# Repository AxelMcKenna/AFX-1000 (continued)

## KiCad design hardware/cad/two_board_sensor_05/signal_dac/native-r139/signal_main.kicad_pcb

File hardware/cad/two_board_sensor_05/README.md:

# TBH05 sensor carrier and magnet escape barrier

**Current spring completion candidate:** see [SPRING.md](SPRING.md) for the selected spring, positive custom clevis-pin anchors, replacement bracket/arm and final `spring-verified-r2` evidence. The r3 carrier below remains unchanged. Its original-anchor spring discussion is retained as reference and superseded by that add-on.

This is a new **unpowered mechanical interface candidate**, fitted to the unchanged TBH01 r6 housing and TBH03 r5 lever. It closes the modeled carrier attachment and adds positive axial magnet capture. It does **not** supply a routed/populated angle-sensor PCB, a qualified magnet bond, or a selected return spring.

The existing source specified a custom AS5600 PCB reserve, not an off-the-shelf board. This design therefore specifies a **new 20 × 18 × 1.6 mm PCB**, instead of guessing holes in an existing board. Its sensor axis is unchanged at Y82/Z31.6. The original 20 mm-tall reserve had insufficient room for an actual top clamp below the button guide; shortening its top edge by 2 mm fixes that interface. A PCB designer must accept and implement this contract before printing for an actual populated board.

## Files and geometry

- `carrier.scad`: editable geometry. `tbh05_installed()` exposes the complete nominal assembly, hardware-head and electrical-envelope allocations for integration. Include the source with a nonmatching `part` selector, or use modules with all inherited housing definitions available.
- `mechanical-contract.json`: dimensions, PCB edge keepouts, component/lead/wiring reserves, fasteners and spring geometry.
- `verified-r3/review.json`: final native cases and recursively bound source hashes. Nine empty interference checks, two printable solids and one positive magnet-capture control.
- `verified-r3/sensor_carrier/sensor_carrier.stl` and `verified-r3/sensor_cap/sensor_cap.stl`: native print candidates, millimetres, base at Z0.
- `preview-r3.png`: exact exported carrier/cap meshes with the nominal custom PCB/package and original lever; omitted wiring/spring/fasteners are identified.
- `analysis.py`, `run.py`, `preview.py`: regenerate scalar evidence, isolated native checks and preview. Run native checks with a fresh output name; prior evidence is never overwritten.

The carrier uses the existing **left lever bolts at (306,69) and (306,102)**. Replace those two M3×20 bolts with **M3×25** and retain 0.5 mm washers, head OD≤5.5 mm and washer OD≤7 mm. The 2 mm feet sit on top of the existing bracket. Screw tips reach Z−4.9, giving 1.1 mm nominal clearance with the existing ≥6 mm feet. Measure actual thread engagement and tip clearance.

Two horizontal **M2×5 screws**, head OD≤3.8 mm and height≤2 mm, secure the removable cap. Tap the two Ø1.6 pilots M2 after printing. The cap enters from above; its tabs lie outside the end rails, so no screw passes through the PCB. Do not substitute taller vertical cap screws: the guide is directly above this assembly. Inspect the thin features, holes and magnet-barrier supports in the slicer; no printer/material process is qualified here.

## Sensor PCB receiving contract

The board is vertical: X299.7..301.3, Y72..92, Z21.6..39.6. It slides into 2 mm-wide X slots with no drilled mounting holes. Nominal 1.6 mm stock and the 1.5–1.7 mm receiving interval leave play; printed dimensions must be measured and shims or a dimensionally corrected carrier used to achieve alignment. Do not infer precise sensor centering from loose slots.

Keep both Y-edge margins and top/bottom margins free of copper, pads and components as specified in the JSON. The sensor and its lands receive a conservative 6.4 × 6.4 mm YZ envelope, projecting 1.75 mm toward +X. That is an allocation, not an approved supplier maximum. The board rear has a 1.5 mm-deep central population/lead reserve and a separate X293.7..299.7/Y76..88/Z23..28 wiring/connector reserve. The eventual board and selected connector must fit those bounds or the carrier must be revised. The rest of the harness is not defined by this local reserve.

Insert the populated board with the cap removed. Its component side faces the magnet (+X). There is no retained board polarity/connector design yet. After assembly, confirm the package center actually aligns to Y82/Z31.6 and measure the magnet/package gap throughout lever endplay.

## Magnet capture and magnetic alignment

A stationary polymer ring lies at X303.5..304.3, with a Ø4 opening in front of the existing Ø6 magnet pocket. It blocks a Ø6 magnet from leaving axially. The ring and both supports are physically part of the carrier, not floating preview geometry. The native positive control overlaps the barrier with an escaping magnet; full lever sweep includes ±0.5 mm axial motion and the earlier 0.1 mm rotor expansion.

**The ring does not transmit torque.** A compatible selected adhesive and verified bond to the rotor are still required; a loose magnet can remain captured while giving a wrong angle. Install and bond the magnet before fitting the carrier. Do not change magnet thickness or polarity silently: the existing pocket is for Ø6 × 2 mm diametric magnetization. Grade, dimensional tolerances, adhesive compatibility, retention under shock and the magnetic field remain unqualified.

At the allocated package face and a nominal seated magnet front of X305.1, the nominal physical gap is 2.05 mm, ranging 1.55–2.55 mm across the ±0.5 mm geometric allowance. This arithmetic does not prove acceptable field strength. The manufacturer's [AS5600 evaluation-board manual](https://look.ams-osram.com/m/4f8342513a447495/original/AS5600_UG000254_2-00.pdf) illustrates a nonmagnetic holder, a 6 × 2.5 mm reference magnet and 0.5–2.5 mm gap; it instructs alignment using the AGC reading. Its reference magnet is **not** the current 2 mm-thick design magnet. Select and test the actual magnet, verify magnet-present/field status and angle through the full stroke, and adjust the carrier if required.

## Return spring: concrete remaining work

The unchanged fixed eye is (316,70,35.6); the rotating eye follows (316,82+10sin(a),31.6+10cos(a)). Eye spacing rises monotonically from **13.4164 to 18.2243 mm** over 0–35°, requiring **4.8079 mm travel**. The restoring moment arm is 8.9443 to 6.6527 mm. `analysis.py` checks the geometry independently; a conservative Ø4.02 mm corridor covers a ≤4 mm spring through continuous motion using hulls between 1° poses (0.01 mm radial reserve exceeds the chord error).

That corridor clears the modeled shell, controls, PCB envelopes and new carrier. It is not the actual spring, hooks or attachment design. The existing Ø2.2 cross holes do not automatically accept a catalogue spring's closed loops. Final spring selection needs the actual hook/clevis attachment geometry, preload, load/stroke rating, fatigue life and desired hand force; then repeat the local anchor/lever interference and physical return tests. The [Lee Spring catalogue](https://www.leespring.fr/download/Lee_Spring_Catalog_US_Eng.pdf) provides dimensional/load candidates, but no catalogue part has been adopted or ordered here.

## Validation scope and remaining gates

Final native evidence checks nominal carrier/cap/PCB allocations and hardware heads against shell, current component/lead envelopes, controls and the expanded moving lever. The intentional bracket seating contact uses the same 0.01 mm contact-plane exclusion as earlier packages. These are geometric checks, not a blanket manufacturing tolerance proof.

Remaining gates are: accept and electrically implement the custom sensor PCB and connector; select magnet/adhesive and exact spring/hooks; verify actual print fit, alignment, AGC/field status, rotation, return force, wear and retention; integrate the full harness. No powered or full-unit fabrication release is claimed. Prior r6/r5 packages were not modified.

Trial01 failed at sandbox Docker socket access and trial02 found the daemon stopped; no CAD process started in either case. These are recorded separately from CAD failures. Trial03 found an actual cap/guide interference; trial04 corrected it, and subsequent revisions strengthened cap screw bosses and added explicit electrical envelopes. Only `verified-r3` is the current evidence.

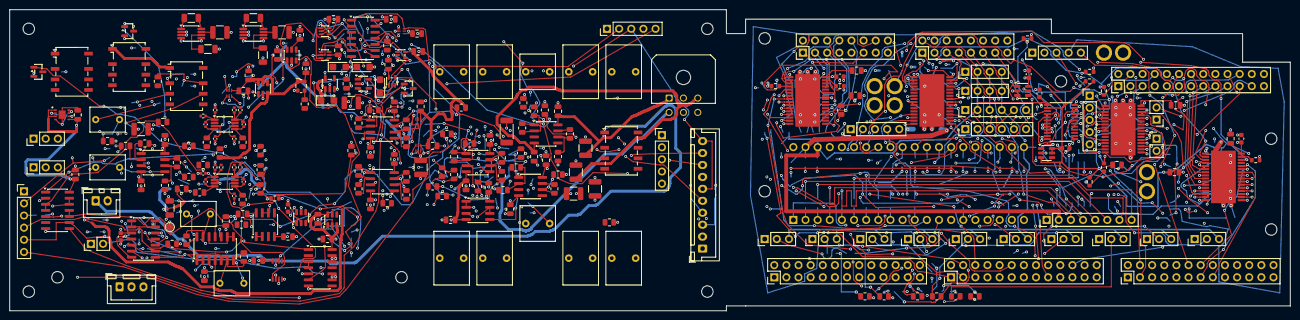
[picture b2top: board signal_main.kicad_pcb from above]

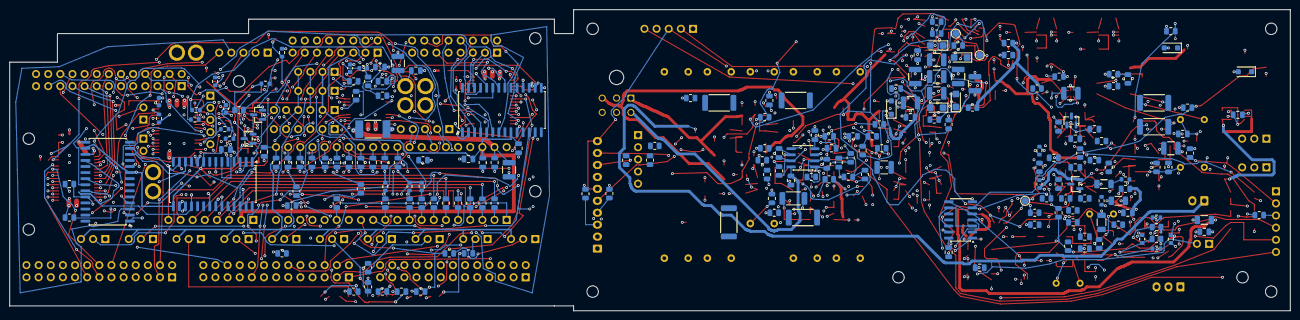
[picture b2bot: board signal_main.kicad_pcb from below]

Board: 8 copper layers, 268.0 x 63.0 mm, 477 parts (202 on the bottom side), 369 nets.

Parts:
A_C101, A_C102, A_C115, A_C116: 1pF C0G +/-0.1pF; C_0402_1005Metric
A_C103, A_C117: 47pF C0G 5%; C_0805_2012Metric
A_C104, A_C105, A_C118, A_C119: 22pF C0G 5%; C_0805_2012Metric
A_C106, A_C120: 100nF 25V X7R; C_0805_2012Metric
A_C107, A_C121: 1uF 63V film 10%; C_Rect_L7.2mm_W5.0mm_P5.00mm
A_C108, A_C122: 10uF 16V X7R; C_1206_3216Metric
A_C109, A_C123: 47uF 25V X7S; C_1210_3225Metric
A_C110, A_C111, A_C124, A_C125: 47uF 6.3V X7S; C_1206_3216Metric
A_C112, A_C126: 2.2uF 16V X7R; C_0805_2012Metric
A_C113, A_C114, A_C127, A_C128: 100nF 16V X7R; C_0402_1005Metric
A_C129, A_C130, A_C131, A_C132, A_C220, A_C221, A_C222, A_C223, A_C224, A_C225, A_C226, A_C228, A_C229, A_C311, A_C312, A_C313, A_C314, A_C315, A_C316, A_C317, A_C318, A_C323, A_C324, A_C405, A_C406, A_C505, A_C506, A_C507, A_C508: 100nF 50V X7R; C_0805_2012Metric
A_C133, A_C134: 10uF 50V X7R; C_1206_3216Metric
A_C135, A_C136: 100nF 16V X7R; C_0603_1608Metric
A_C201, A_C202, A_C205: 1uF 10V X7R 10%; C_0805_2012Metric
A_C203, A_C210, A_C212, A_C214: 100nF 50V C0G 5%; C_1210_3225Metric
A_C204, A_C206, A_C207, A_C208, A_C209, A_C211, A_C213, A_C215: 1uF 10V tantalum 10%; CP_EIA-3216-18_Kemet-A
A_C216, A_C218, A_C227: 2.2uF 25V X7R 10%; C_1210_3225Metric
A_C217, A_C219: 10uF 16V X7R 10%; C_1210_3225Metric
A_C230, A_C231, A_C232, A_C610, A_C611, A_C612: 100nF 16V X7R; C_0805_2012Metric
A_C301, A_C302, A_C306, A_C307: 510pF 50V C0G 2%; C_0805_2012Metric
A_C303, A_C308: 51pF 50V C0G 2%; C_0805_2012Metric
A_C304, A_C305, A_C309, A_C310: 1nF 50V C0G 1%; C_0805_2012Metric
A_C319, A_C320, A_C509, A_C510, A_C511, A_C512: 10uF 50V X7R; C_1210_3225Metric
A_C321, A_C322: 2.2uF film 63V 10%; C_Rect_L7.2mm_W7.2mm_P5.00mm_FKS2_FKP2_MKS2_MKP2
A_C401, A_C403: 1uF film 63V 10%; C_Rect_L7.2mm_W5.0mm_P5.00mm
A_C402, A_C404: 47pF 50V C0G 5%; C_0805_2012Metric
A_C407, A_C408: 10uF 50V X7R 10%; C_1210_3225Metric
A_C501, A_C502, A_C503, A_C504, A_C513, A_C514, A_C515, A_C516: 4.7uF film 63V 10%; C_Rect_L7.2mm_W11.0mm_P5.00mm_FKS2_FKP2_MKS2_MKP2
A_C601: 150pF C0G 5%; C_0805_2012Metric
A_C602, A_C603, A_C604, A_C605, A_C606: 100nF X7R; C_0805_2012Metric
A_C607: 1uF 16V X7R; C_0805_2012Metric
A_C608: 22uF 16V X7R; C_1206_3216Metric
A_C609: 1uF 16V X7R 10%; C_0805_2012Metric
A_D101, A_D102: BAT54S,215; SOT-23
A_D601, A_D602, A_D603: SMF9.0A; D_SOD-123F
A_H1, A_H2, A_H3, A_H4: M2_CLEARANCE; M2_Clearance
A_H5, A_H6: M2_SHARED_SUPPORT; M2_Clearance
A_J203, A_J603: Conn_01x05; PinHeader_1x05_P2.54mm_Vertical
A_J402: B10B-XH-A(LF)(SN); JST_XH_B10B-XH-A_1x10_P2.50mm_Vertical
A_J403: B3B-XH-A(LF)(SN); JST_XH_B3B-XH-A_1x03_P2.50mm_Vertical
A_J602: Conn_01x06; PinHeader_1x06_P2.54mm_Vertical
A_J606: Conn_01x02; PinHeader_1x02_P2.54mm_Vertical
A_J607, A_J608: Conn_01x03; PinHeader_1x03_P2.54mm_Vertical
A_J701: 43045-0600; Molex_Micro-Fit_3.0_43045-0600_2x03_P3.00mm_Horizontal
A_J702: B2B-XH-A(LF)(SN); JST_XH_B2B-XH-A_1x02_P2.50mm_Vertical
A_K401, A_K503, A_K601, A_K602: G6K-2F-Y DC5; Relay_DPDT_Omron_G6K-2F-Y
A_Q601, A_Q602, A_Q603: AO3400A; SOT-23
A_R101, A_R102, A_R117, A_R118: 2.49k 0.05%; R_0402_1005Metric
A_R103, A_R104, A_R119, A_R120: 1.21k 0.05%; R_0402_1005Metric
A_R105, A_R106, A_R121, A_R122: 3.3R 1%; R_0805_2012Metric
A_R107, A_R123: 1M 1%; R_0805_2012Metric
A_R108, A_R109, A_R124, A_R125: 100k 0.01%; R_0805_2012Metric
A_R110, A_R111, A_R126, A_R127, A_R212: 10k 0.1%; R_0805_2012Metric
A_R112, A_R128: 10M 1%; R_0805_2012Metric
A_R113, A_R129, A_R203, A_R204, A_R601, A_R606: 10k 1%; R_0805_2012Metric
A_R114, A_R130, A_R205, A_R206, A_R603, A_R604, A_R605, A_R607, A_R615: 47k 1%; R_0805_2012Metric
A_R115, A_R131: 68k 1%; R_0805_2012Metric
A_R116, A_R132: 0.1R 1%; R_0805_2012Metric
A_R133: 1k 1%; R_0805_2012Metric
A_R134, A_R136: 100k 0.01%; R_0603_1608Metric
A_R135, A_R137, A_R139, A_R141: 10k 0.01%; R_0603_1608Metric
A_R138: 161k 0.01%; R_0805_2012Metric
A_R140: 240k 0.01%; R_0805_2012Metric
A_R142, A_R143: 10k 1%; R_0603_1608Metric
A_R144: 100k 1%; R_0603_1608Metric
A_R201, A_R202: 2k 1%; R_0805_2012Metric
A_R207, A_R208, A_R209, A_R210, A_R517, A_R518, A_R602, A_R617, A_R618: 100k 1%; R_0805_2012Metric
A_R211: 27.7k 0.1%; R_0805_2012Metric
A_R213, A_R214, A_R215, A_R216: 33 1%; R_0805_2012Metric
A_R301, A_R302, A_R313, A_R314: 1.8k 0.1%; R_0805_2012Metric
A_R303, A_R304, A_R315, A_R316: 4.3 1%; R_0805_2012Metric
A_R305, A_R306, A_R317, A_R318: 100k 0.1%; R_0805_2012Metric
A_R307, A_R319: 1.2M 0.1%; R_0805_2012Metric
A_R308, A_R309, A_R310, A_R311, A_R320, A_R321, A_R322, A_R323: 499 0.01%; R_0805_2012Metric
A_R312, A_R324, A_R407, A_R414: 33.2 0.1%; R_0805_2012Metric
A_R325, A_R326, A_R401, A_R408: 33.2k 0.1%; R_0805_2012Metric
A_R327, A_R328: 2.74k 0.1% 0.5W; R_2010_5025Metric
A_R402, A_R409: 13.7k 0.1%; R_0805_2012Metric
A_R403, A_R410: 4.99k 0.1% 1W; R_2512_6332Metric
A_R404, A_R411: 68k 0.1%; R_0805_2012Metric
A_R405, A_R412: 365 0.1%; R_0805_2012Metric
A_R406, A_R413, A_R502, A_R506: 1k 0.1%; R_0805_2012Metric
A_R501, A_R505: 5.23k 0.1%; R_0805_2012Metric
A_R503, A_R507, A_R511, A_R515: 100 1% 1W; R_2512_6332Metric
A_R504, A_R508, A_R512, A_R516: 20k 1%; R_0805_2012Metric
A_R509, A_R513: 1.21k 0.1%; R_0805_2012Metric
A_R510, A_R514: 2k 0.1%; R_0805_2012Metric
A_R608, A_R610, A_R612: 4.7k 1%; R_0805_2012Metric
A_R609, A_R611, A_R613: 270k 1%; R_0805_2012Metric
A_R614: 383k 0.1% 25ppm; R_0805_2012Metric
A_R616: 147k 1%; R_0805_2012Metric
A_TP401: TEST_ONLY_ADC_DRV_ENABLE; TestPoint_Pad_D1.5mm
A_TP402: TEST_ONLY_CHIP_EN; TestPoint_Pad_D1.5mm
A_TP403: TEST_ONLY_PD_GATED; TestPoint_Pad_D1.5mm
A_TP404: TEST_ONLY_AGND; TestPoint_Pad_D1.5mm
A_U101, A_U102: THS4551IDGKR; VSSOP-8_3x3mm_P0.65mm
A_U103, A_U305, A_U401: OPA1656ID; SOIC-8_3.9x4.9mm_P1.27mm
A_U104: OPA4192ID; SOIC-14_3.9x8.7mm_P1.27mm
A_U105, A_U106: LM7705MM/NOPB; VSSOP-8_3x3mm_P0.65mm
A_U107: TLV9024DR; SOIC-14_3.9x8.7mm_P1.27mm
A_U108, A_U605: TPS3808G50DBVR; SOT-23-6
A_U202: TPS7A2033PDBVR; SOT-23-5
A_U203: TPS7A2045PDBVR; SOT-23-5
A_U204, A_U205, A_U208: TPS389033DSET; TI_DSE0006A_TPS3890
A_U206: TPS389001DSET; TI_DSE0006A_TPS3890
A_U207, A_U602, A_U606: SN74HCS08DR; SOIC-14_3.9x8.7mm_P1.27mm
A_U209, A_U212: SN74LVC1G08DCKR; SOT-353_SC-70-5
A_U210: SN74LVC2G17DCKR; SOT-363_SC-70-6
A_U211: SN74LVC1G17DCKR; SOT-353_SC-70-5
A_U301, A_U302, A_U303, A_U304, A_U502: OPA1612AID; SOIC-8_3.9x4.9mm_P1.27mm
A_U501: OPA2992D; SOIC-8_3.9x4.9mm_P1.27mm
A_U601: TPS3431SDRBR; TI_DRB0008A_TPS3431
A_U603: SN74LVC1G74DCTR; TI_DCT0008A_SN74LVC1G74
A_U604: TPS3808G33DBVR; SOT-23-6
A_U607: LTC6994HS6-1#TRMPBF; TSOT-23-6
A_U608: SN74HCS86DR; SOIC-14_3.9x8.7mm_P1.27mm
A_Y201: ECS-2520MVLC-245.7-BN-TR; Oscillator_SMD_ECS_2520MV-xxx-xx-4Pin_2.5x2.0mm
D_C1001, D_C3013: 22uF 25V X7R; C_1210_3225Metric
D_C1002, D_C1004, D_C1006, D_C1011, D_C1012, D_C1013, D_C1014, D_C1015, D_C1016, D_C1017, D_C1018, D_C1019, D_C1020, D_C2001, D_C2002, D_C2003: 100nF 16V X7R; C_0805_2012Metric
D_C1003, D_C2004: 1uF 16V X7R; C_0805_2012Metric
D_C1005, D_C3002, D_C3004, D_C3006, D_C3008, D_C3014: 4.7uF 16V X7R; C_0805_2012Metric
D_C3001, D_C3003, D_C3005, D_C3007, D_C3009, D_C3010, D_C3011, D_C3012: 100nF 16V X7R; C_0603_1608Metric
D_H1, D_H2, D_H3, D_H4, D_H5: M2_CLEARANCE; M2_Clearance
D_J1001, D_J1013, D_J1014, D_J1015: Alpha6715_AWG18_DIRECT_SOLDER_PROPOSAL; AWG18_Solder_2x1_P4mm_D2p2
D_J1003, D_J1006: Header6; PinHeader_1x06_P2.54mm_Vertical
D_J1004, D_J1005, D_J2003: Header5; PinHeader_1x05_P2.54mm_Vertical
D_J1007, D_J1008: Header2; PinHeader_1x02_P2.54mm_Vertical
D_J1009, D_J1010: Header4; PinHeader_1x04_P2.54mm_Vertical
D_J1012: Header8; PinHeader_1x08_P2.54mm_Vertical
D_J1020, D_J1021, D_J1022, D_J1023, D_J1024, D_J1025, D_J1026, D_J1027, D_J1028, D_J1029: Header3; PinHeader_1x03_P2.54mm_Vertical
D_J2001, D_J2002: Header16; PinHeader_2x08_P2.54mm_Vertical
D_J3002, D_J3003, D_J3004, D_J3005: Header26; PinHeader_2x13_P2.54mm_Vertical
D_Q3001, D_Q3002: AO3400A; SOT-23
D_R1001: 0.47R 1% WSLT2512R4700FEA P70=0.815W; WSLT2512_R_2512_Manufacturer
D_R1002: 10k 1%; R_0805_2012Metric
D_R1003, D_R1004, D_R1005, D_R1006, D_R2001: 100k 1%; R_0805_2012Metric
D_R1010, D_R1011, D_R1012, D_R1013, D_R1014, D_R1015, D_R1016, D_R1017, D_R1018, D_R1019, D_R1020: 33R 1%; R_0805_2012Metric
D_R1031, D_R1032, D_R1033, D_R1034, D_R1035, D_R1036, D_R1037, D_R1038, D_R1039, D_R1040: 1k 1%; R_0805_2012Metric
D_R1041, D_R1042, D_R1043, D_R1044, D_R1045, D_R1046, D_R1047, D_R1048, D_R1049, D_R1050: 1M 1%; R_0805_2012Metric
D_R2002: 47k 1%; R_0805_2012Metric
D_R2003: 270k 1%; R_0805_2012Metric
D_R3001, D_R3002, D_R3003, D_R3004: 16.5k 1%; R_0603_1608Metric
D_R3005: 47k 1%; R_0603_1608Metric
D_R3006, D_R3007, D_R3010, D_R3011: 10k 1%; R_0603_1608Metric
D_R3008, D_R3009, D_R3012, D_R3013, D_R3014, D_R3019, D_R3020, D_R3021: 100k 1%; R_0603_1608Metric
D_R3015, D_R3016, D_R3017, D_R3018: 33R 1%; R_0603_1608Metric
D_U1001: DaisySeed3; Seed3_Socket40
D_U2001, D_U2002, D_U2003: MCP23017-E/SO; SOIC-28W_7.5x17.9mm_P1.27mm
D_U3001, D_U3002, D_U3003, D_U3004: TLC5947DAPR; TLC5947_DAP0032C
D_U3005: SN74LVC8T245PWR; TSSOP-24_4.4x7.8mm_P0.65mm
D_U3006: TPS3808G33DBVR; SOT-23-6
D_U3007: TPS3808G50DBVR; SOT-23-6

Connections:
/A_ADC/BIAS_SHIFT_L: A_R134.2, A_R135.1, A_U107.4, A_U107.7
/A_ADC/BIAS_SHIFT_R: A_R136.2, A_R137.1, A_U107.8, A_U107.11
/A_ADC/BUF_L: A_R101.1, A_U103.1, A_U103.2
/A_ADC/BUF_R: A_R117.1, A_U103.6, A_U103.7
/A_ADC/CM_DRIVE_L: A_C107.1, A_R112.1, A_R113.1, A_U104.7
/A_ADC/CM_DRIVE_R: A_C121.1, A_R128.1, A_R129.1, A_U104.14
/A_ADC/CM_SENSE_L: A_C107.2, A_R110.2, A_R111.2, A_R112.2, A_U104.6
/A_ADC/CM_SENSE_R: A_C121.2, A_R126.2, A_R127.2, A_R128.2, A_U104.13
/A_ADC/DRV_LN: A_C101.1, A_R106.1, A_U101.5
/A_ADC/DRV_LP: A_C102.1, A_R105.1, A_U101.4
/A_ADC/DRV_RN: A_C115.1, A_R122.1, A_U102.5
/A_ADC/DRV_RP: A_C116.1, A_R121.1, A_U102.4
/A_ADC/FB_N_L: A_C102.2, A_R102.2, A_R104.2, A_U101.1
/A_ADC/FB_N_R: A_C116.2, A_R118.2, A_R120.2, A_U102.1
/A_ADC/FB_P_L: A_C101.2, A_R101.2, A_R103.2, A_U101.8
/A_ADC/FB_P_R: A_C115.2, A_R117.2, A_R119.2, A_U102.8
/A_ADC/FLY_N_L: A_C108.2, A_U105.8
/A_ADC/FLY_N_R: A_C122.2, A_U106.8
/A_ADC/FLY_P_L: A_C108.1, A_U105.1
/A_ADC/FLY_P_R: A_C122.1, A_U106.1
/A_ADC/NBIAS_L: A_C111.1, A_C114.1, A_J403.2, A_R115.2, A_R116.2, A_R135.2, A_U101.6
/A_ADC/NBIAS_R: A_C125.1, A_C128.1, A_J403.3, A_R131.2, A_R132.2, A_R137.2, A_U102.6
/A_ADC/NPUMP_L: A_C110.1, A_R116.1, A_U105.6
/A_ADC/NPUMP_R: A_C124.1, A_R132.1, A_U106.6
/A_ADC/PD_GATED: A_R114.1, A_R130.1, A_R143.2, A_R144.1, A_TP403.1, A_U108.1
/A_ADC/PD_L: A_R114.2, A_R115.1, A_U101.7
/A_ADC/PD_R: A_R130.2, A_R131.1, A_U102.7
/A_ADC/REF_DIV_L: A_C106.1, A_R108.2, A_R109.1, A_U104.3
/A_ADC/REF_DIV_R: A_C120.1, A_R124.2, A_R125.1, A_U104.10
/A_ADC/REF_HALF_L: A_U104.1, A_U104.2, A_U104.5
/A_ADC/REF_HALF_R: A_U104.8, A_U104.9, A_U104.12
/A_ADC/RES_L: A_C109.1, A_U105.7
/A_ADC/RES_R: A_C123.1, A_U106.7
/A_ADC/THRESH_LOWER: A_R140.2, A_R141.1, A_U107.6, A_U107.10
/A_ADC/THRESH_UPPER: A_R138.2, A_R139.1, A_U107.5, A_U107.9
/A_ADC/VOCM_L: A_D101.3, A_R113.2, A_U101.2
/A_ADC/VOCM_R: A_D102.3, A_R129.2, A_U102.2
/A_BYPASS/BYPASS_GATE: A_Q601.1, A_R608.2, A_R609.1
/A_BYPASS/BYPASS_LOW: A_D601.1, A_K601.8, A_Q601.3
/A_BYPASS/CLEAR_N: A_U603.6, A_U606.5, A_U606.8
/A_BYPASS/COIL_ENABLE: A_U602.8, A_U606.4
/A_BYPASS/CWD: A_C601.1, A_U601.2
/A_BYPASS/FINAL_ENABLE: A_R608.1, A_U606.6
/A_BYPASS/GAIN_DELAY: A_C609.1, A_R615.2, A_U608.2
/A_BYPASS/GAIN_EDGE: A_U608.3, A_U608.4
/A_BYPASS/GAIN_GATE: A_Q602.1, A_R610.2, A_R611.1
/A_BYPASS/GAIN_STABLE: A_U606.13, A_U608.6
/A_BYPASS/INPUT_ENABLE: A_R612.1, A_U602.3, A_U602.4, A_U606.12
/A_BYPASS/INPUT_GATE: A_Q603.1, A_R612.2, A_R613.1
/A_BYPASS/INPUT_LOW: A_D603.1, A_K602.8, A_Q603.3
/A_BYPASS/IN_L: A_J607.1, A_K601.2, A_K602.4
/A_BYPASS/IN_R: A_J607.3, A_K601.7, A_K602.5
/A_BYPASS/LOCAL_OK: A_R601.2, A_U601.7, A_U601.8, A_U602.1, A_U604.1, A_U605.1
/A_BYPASS/OUT_L: A_J608.1, A_K601.3
/A_BYPASS/OUT_R: A_J608.3, A_K601.6
/A_BYPASS/PERMIT_CLEAN: A_U602.10, A_U602.11, A_U603.1
/A_BYPASS/PROCESS_HEALTH: A_U602.6, A_U606.10
/A_BYPASS/PROCESS_OK: A_J603.2, A_R604.1, A_U602.5
/A_BYPASS/STARTUP_CT: A_R618.2, A_U604.4
/A_BYPASS/TIMER_DIV: A_R616.2, A_R617.1, A_U607.4
/A_BYPASS/TIMER_ENABLE: A_U606.1, A_U606.11, A_U607.1
/A_BYPASS/TIMER_INPUT_OK: A_U606.2, A_U607.6
/A_BYPASS/TIMER_SET: A_R614.1, A_U607.3
/A_CODEC/A3V3: A_C205.1, A_C217.1, A_C229.1, A_U202.5, A_U205.1
/A_CODEC/A4V5: A_C207.1, A_C219.1, A_R211.1, A_U203.5
/A_CODEC/ADC_BIAS_IO: A_U211.4, A_U212.2
/A_CODEC/CHIP_REQUEST: A_U207.6, A_U210.1
/A_CODEC/CLK_VALID: A_R207.1, A_U207.9
/A_CODEC/CODEC_FLAGS: A_U207.8, A_U207.13
/A_CODEC/CODEC_PGOOD: A_J402.9, A_R203.1, A_U204.6, A_U205.6, A_U206.6, A_U207.1
/A_CODEC/CT_SETTLE: A_C227.1, A_U208.5
/A_CODEC/DRIVER_SETTLE_READY: A_U208.3, A_U209.1, A_U212.4
/A_CODEC/MCLK_SRC: A_R213.1, A_Y201.3
/A_CODEC/PRE_ANALOG_OK: A_J402.8, A_R206.1, A_U207.2
/A_CODEC/RAMP_DONE: A_R208.1, A_U207.10
/A_CODEC/REF_DAC_BUF: A_C203.1, A_C204.1
/A_CODEC/REF_PLL: A_C210.1, A_C211.1
/A_CODEC/SENSE_4V5: A_R211.2, A_R212.1, A_U206.1
/A_CODEC/SETTLE_ENABLE: A_U207.11, A_U210.3, A_U212.1
/A_CODEC/SUPPLY_OK: A_U207.3, A_U207.4
/A_CODEC/TIMER_OK: A_R204.1, A_U208.6, A_U209.2
/A_DAC/BIAS_N_L: A_R304.2, A_U301.5
/A_DAC/BIAS_N_R: A_R316.2, A_U302.5
/A_DAC/BIAS_P_L: A_R303.2, A_U301.3
/A_DAC/BIAS_P_R: A_R315.2, A_U302.3
/A_DAC/BUF_IN_L: A_R327.2, A_U305.3
/A_DAC/BUF_IN_R: A_R328.2, A_U305.5
/A_DAC/BUF_OUT_L: A_R312.1, A_U305.1, A_U305.2
/A_DAC/BUF_OUT_R: A_R324.1, A_U305.6, A_U305.7
/A_DAC/CM_DRV_L: A_C303.2, A_R303.1, A_R304.1, A_R307.2, A_U303.1
/A_DAC/CM_DRV_R: A_C308.2, A_R315.1, A_R316.1, A_R319.2, A_U303.7
/A_DAC/CM_SUM_L: A_C303.1, A_R305.2, A_R306.2, A_R307.1, A_U303.2
/A_DAC/CM_SUM_R: A_C308.1, A_R317.2, A_R318.2, A_R319.1, A_U303.6
/A_DAC/HP_NODE_L: A_C321.2, A_R325.1, A_R327.1
/A_DAC/HP_NODE_R: A_C322.2, A_R326.1, A_R328.1
/A_DAC/IV_N_L: A_C302.2, A_R302.2, A_R306.1, A_R309.1, A_U301.7
/A_DAC/IV_N_R: A_C307.2, A_R314.2, A_R318.1, A_R321.1, A_U302.7
/A_DAC/IV_P_L: A_C301.2, A_R301.2, A_R305.1, A_R308.1, A_U301.1
/A_DAC/IV_P_R: A_C306.2, A_R313.2, A_R317.1, A_R320.1, A_U302.1
/A_DAC/RX_NEG_L: A_C304.1, A_R308.2, A_R310.1, A_U304.2
/A_DAC/RX_NEG_R: A_C309.1, A_R320.2, A_R322.1, A_U304.6
/A_DAC/RX_OUT_L: A_C304.2, A_C321.1, A_R310.2, A_U304.1
/A_DAC/RX_OUT_R: A_C309.2, A_C322.1, A_R322.2, A_U304.7
/A_DAC/RX_POS_L: A_C305.1, A_R309.2, A_R311.1, A_U304.3
/A_DAC/RX_POS_R: A_C310.1, A_R321.2, A_R323.1, A_U304.5
/A_INPUT/ATTN_L: A_K401.2, A_R401.2, A_R402.1
/A_INPUT/ATTN_R: A_K401.7, A_R408.2, A_R409.1
/A_INPUT/BUF_IN_L: A_C401.2, A_C402.1, A_R404.1, A_U401.3
/A_INPUT/BUF_IN_R: A_C403.2, A_C404.1, A_R411.1, A_U401.5
/A_INPUT/BUF_OUT_L: A_R405.2, A_R407.1, A_U401.1
/A_INPUT/BUF_OUT_R: A_R412.2, A_R414.1, A_U401.7
/A_INPUT/GAIN_FB_L: A_R405.1, A_R406.1, A_U401.2
/A_INPUT/GAIN_FB_R: A_R412.1, A_R413.1, A_U401.6
/A_INPUT/HP_SRC_L: A_C401.1, A_R403.2
/A_INPUT/HP_SRC_R: A_C403.1, A_R410.2
/A_INPUT/RANGE_L: A_K401.3, A_R403.1
/A_INPUT/RANGE_R: A_K401.6, A_R410.1
/A_OUTPUT/M_AC_L: A_C501.2, A_C513.2, A_K503.2, A_R504.1
/A_OUTPUT/M_AC_R: A_C502.2, A_C514.2, A_K503.7, A_R508.1
/A_OUTPUT/M_DRV_L: A_R501.2, A_R503.1, A_U501.1
/A_OUTPUT/M_DRV_R: A_R505.2, A_R507.1, A_U501.7
/A_OUTPUT/M_FB_L: A_R501.1, A_R502.1, A_U501.2
/A_OUTPUT/M_FB_R: A_R505.1, A_R506.1, A_U501.6
/A_OUTPUT/M_SER_L: A_C501.1, A_C513.1, A_R503.2
/A_OUTPUT/M_SER_R: A_C502.1, A_C514.1, A_R507.2
/A_OUTPUT/S_AC_L: A_C503.2, A_C515.2, A_K503.4, A_R512.1
/A_OUTPUT/S_AC_R: A_C504.2, A_C516.2, A_K503.5, A_R516.1
/A_OUTPUT/S_DRV_L: A_R509.2, A_R511.1, A_U502.1
/A_OUTPUT/S_DRV_R: A_R513.2, A_R515.1, A_U502.7
/A_OUTPUT/S_FB_L: A_R509.1, A_R510.1, A_U502.2
/A_OUTPUT/S_FB_R: A_R513.1, A_R514.1, A_U502.6
/A_OUTPUT/S_SER_L: A_C503.1, A_C515.1, A_R511.2
/A_OUTPUT/S_SER_R: A_C504.1, A_C516.1, A_R515.2
/D_CONTROLS/CONTROL_00: D_J2001.13, D_U2001.21
/D_CONTROLS/CONTROL_01: D_J2001.11, D_U2001.22
/D_CONTROLS/CONTROL_02: D_J2001.9, D_U2001.23
/D_CONTROLS/CONTROL_03: D_J2001.7, D_U2001.24
/D_CONTROLS/CONTROL_04: D_J2001.5, D_U2001.25
/D_CONTROLS/CONTROL_05: D_J2001.3, D_U2001.26
/D_CONTROLS/CONTROL_06: D_J2001.1, D_U2001.27
/D_CONTROLS/CONTROL_07: D_J2001.2, D_U2001.1
/D_CONTROLS/CONTROL_08: D_J2001.4, D_U2001.2
/D_CONTROLS/CONTROL_09: D_J2001.6, D_U2001.3
/D_CONTROLS/CONTROL_10: D_J2001.8, D_U2001.4
/D_CONTROLS/CONTROL_11: D_J2001.10, D_U2001.5
/D_CONTROLS/CONTROL_12: D_J2001.12, D_U2001.6
/D_CONTROLS/CONTROL_13: D_J2001.14, D_U2001.7
/D_CONTROLS/CONTROL_14: D_J2002.13, D_U2002.21
/D_CONTROLS/CONTROL_15: D_J2002.11, D_U2002.22
/D_CONTROLS/CONTROL_16: D_J2002.9, D_U2002.23
/D_CONTROLS/CONTROL_17: D_J2002.7, D_U2002.24
/D_CONTROLS/CONTROL_18: D_J2002.5, D_U2002.25
/D_CONTROLS/CONTROL_19: D_J2002.3, D_U2002.26
/D_CONTROLS/CONTROL_20: D_J2002.1, D_U2002.27
/D_CONTROLS/CONTROL_21: D_J2002.2, D_U2002.1
/D_CONTROLS/CONTROL_22: D_J2002.4, D_U2002.2
/D_CONTROLS/CONTROL_23: D_J2002.6, D_U2002.3
/D_CONTROLS/CONTROL_24: D_J2002.8, D_U2002.4
/D_CONTROLS/CONTROL_25: D_J2002.10, D_U2002.5
/D_CONTROLS/CONTROL_26: D_J2002.12, D_U2002.6
/D_CONTROLS/CONTROL_27: D_J2002.14, D_U2002.7
/D_CONTROLS/CONTROL_28: D_J2003.2, D_U2003.1
/D_CONTROLS/CONTROL_29: D_J2003.3, D_U2003.2
/D_CONTROLS/CONTROL_30: D_J2003.4, D_U2003.3
/D_CONTROLS/CONTROL_31: D_J2003.5, D_U2003.4
/D_LED/BLANK_5V: D_R3011.1, D_R3018.2, D_U3001.2, D_U3002.2, D_U3003.2, D_U3004.2
/D_LED/BLANK_5V_SRC: D_R3018.1, D_U3005.18
/D_LED/CLOCK_5V: D_R3013.1, D_R3016.2, D_U3001.3, D_U3002.3, D_U3003.3, D_U3004.3
/D_LED/CLOCK_5V_SRC: D_R3016.1, D_U3005.20
/D_LED/DATA_5V: D_R3012.1, D_R3015.2, D_U3001.4
/D_LED/DATA_5V_SRC: D_R3015.1, D_U3005.21
/D_LED/ENABLE_MID: D_Q3001.2, D_Q3002.3
/D_LED/IREF_0: D_R3001.1, D_U3001.31
/D_LED/IREF_1: D_R3002.1, D_U3002.31
/D_LED/IREF_2: D_R3003.1, D_U3003.31
/D_LED/IREF_3: D_R3004.1, D_U3004.31
/D_LED/LATCH_5V: D_R3014.1, D_R3017.2, D_U3001.30, D_U3002.30, D_U3003.30, D_U3004.30
/D_LED/LATCH_5V_SRC: D_R3017.1, D_U3005.19
/D_LED/LED_00: D_J3003.1, D_U3001.5
/D_LED/LED_01: D_J3003.2, D_U3001.6
/D_LED/LED_02: D_J3003.3, D_U3001.7
/D_LED/LED_03: D_J3003.4, D_U3001.8
/D_LED/LED_04: D_J3003.5, D_U3001.9
/D_LED/LED_05: D_J3003.6, D_U3001.10
/D_LED/LED_06: D_J3003.7, D_U3001.11
/D_LED/LED_07: D_J3003.8, D_U3001.12
/D_LED/LED_08: D_J3003.9, D_U3001.13
/D_LED/LED_09: D_J3003.10, D_U3001.14
/D_LED/LED_10: D_J3003.11, D_U3001.15
/D_LED/LED_11: D_J3003.12, D_U3001.16
/D_LED/LED_12: D_J3002.12, D_U3001.17
/D_LED/LED_13: D_J3002.11, D_U3001.18
/D_LED/LED_14: D_J3002.10, D_U3001.19
/D_LED/LED_15: D_J3002.9, D_U3001.20
/D_LED/LED_16: D_J3002.8, D_U3001.21
/D_LED/LED_17: D_J3002.7, D_U3001.22
/D_LED/LED_18: D_J3002.6, D_U3001.23
/D_LED/LED_19: D_J3002.5, D_U3001.24
/D_LED/LED_20: D_J3002.4, D_U3001.25
/D_LED/LED_21: D_J3002.3, D_U3001.26
/D_LED/LED_22: D_J3002.2, D_U3001.27
/D_LED/LED_23: D_J3002.1, D_U3001.28
/D_LED/LED_24: D_J3003.13, D_U3002.5
/D_LED/LED_25: D_J3003.14, D_U3002.6
/D_LED/LED_26: D_J3003.15, D_U3002.7
/D_LED/LED_27: D_J3003.16, D_U3002.8
/D_LED/LED_28: D_J3003.17, D_U3002.9
/D_LED/LED_29: D_J3003.18, D_U3002.10
/D_LED/LED_30: D_J3003.19, D_U3002.11
/D_LED/LED_31: D_J3003.20, D_U3002.12
/D_LED/LED_32: D_J3003.21, D_U3002.13
/D_LED/LED_33: D_J3003.22, D_U3002.14
/D_LED/LED_34: D_J3003.23, D_U3002.15
/D_LED/LED_35: D_J3003.24, D_U3002.16
/D_LED/LED_36: D_J3002.24, D_U3002.17
/D_LED/LED_37: D_J3002.23, D_U3002.18
/D_LED/LED_38: D_J3002.22, D_U3002.19
/D_LED/LED_39: D_J3002.21, D_U3002.20
/D_LED/LED_40: D_J3002.20, D_U3002.21
/D_LED/LED_41: D_J3002.19, D_U3002.22
/D_LED/LED_42: D_J3002.18, D_U3002.23
/D_LED/LED_43: D_J3002.17, D_U3002.24
/D_LED/LED_44: D_J3002.16, D_U3002.25
/D_LED/LED_45: D_J3002.15, D_U3002.26
/D_LED/LED_46: D_J3002.14, D_U3002.27
/D_LED/LED_47: D_J3002.13, D_U3002.28
/D_LED/LED_48: D_J3005.1, D_U3003.5
/D_LED/LED_49: D_J3005.2, D_U3003.6
/D_LED/LED_50: D_J3005.3, D_U3003.7
/D_LED/LED_51: D_J3005.4, D_U3003.8
/D_LED/LED_52: D_J3005.5, D_U3003.9
/D_LED/LED_53: D_J3005.6, D_U3003.10
/D_LED/LED_54: D_J3005.7, D_U3003.11
/D_LED/LED_55: D_J3005.8, D_U3003.12
/D_LED/LED_56: D_J3005.9, D_U3003.13
/D_LED/LED_57: D_J3005.10, D_U3003.14
/D_LED/LED_58: D_J3005.11, D_U3003.15
/D_LED/LED_59: D_J3005.12, D_U3003.16
/D_LED/LED_60: D_J3004.12, D_U3003.17
/D_LED/LED_61: D_J3004.11, D_U3003.18
/D_LED/LED_62: D_J3004.10, D_U3003.19
/D_LED/LED_63: D_J3004.9, D_U3003.20
/D_LED/LED_64: D_J3004.8, D_U3003.21
/D_LED/LED_65: D_J3004.7, D_U3003.22
/D_LED/LED_66: D_J3004.6, D_U3003.23
/D_LED/LED_67: D_J3004.5, D_U3003.24
/D_LED/LED_68: D_J3004.4, D_U3003.25
/D_LED/LED_69: D_J3004.3, D_U3003.26
/D_LED/LED_70: D_J3004.2, D_U3003.27
/D_LED/LED_71: D_J3004.1, D_U3003.28
/D_LED/LED_72: D_J3005.13, D_U3004.5
/D_LED/LED_73: D_J3005.14, D_U3004.6
/D_LED/LED_74: D_J3005.15, D_U3004.7
/D_LED/LED_75: D_J3005.16, D_U3004.8
/D_LED/LED_76: D_J3005.17, D_U3004.9
/D_LED/LED_77: D_J3005.18, D_U3004.10
/D_LED/LED_78: D_J3005.19, D_U3004.11
/D_LED/LED_79: D_J3005.20, D_U3004.12
/D_LED/LED_80: D_J3005.21, D_U3004.13
/D_LED/LED_81: D_J3005.22, D_U3004.14
/D_LED/LED_82: D_J3005.23, D_U3004.15
/D_LED/LED_83: D_J3005.24, D_U3004.16
/D_LED/LED_84: D_J3004.24, D_U3004.17
/D_LED/LED_85: D_J3004.23, D_U3004.18
/D_LED/LED_86: D_J3004.22, D_U3004.19
/D_LED/LED_87: D_J3004.21, D_U3004.20
/D_LED/LED_88: D_J3004.20, D_U3004.21
/D_LED/LED_89: D_J3004.19, D_U3004.22
/D_LED/LED_90: D_J3004.18, D_U3004.23
/D_LED/LED_91: D_J3004.17, D_U3004.24
/D_LED/LED_92: D_J3004.16, D_U3004.25
/D_LED/LED_93: D_J3004.15, D_U3004.26
/D_LED/LED_94: D_J3004.14, D_U3004.27
/D_LED/LED_95: D_J3004.13, D_U3004.28
/D_LED/OE_N: D_Q3001.3, D_R3005.1, D_U3005.22
/D_LED/PG_3V3: D_Q3001.1, D_R3006.1, D_R3008.1, D_U3006.1
/D_LED/PG_5V: D_Q3002.1, D_R3007.1, D_R3009.1, D_U3007.1
/D_LED/SERIAL_0: D_U3001.29, D_U3002.4
/D_LED/SERIAL_1: D_U3002.29, D_U3003.4
/D_LED/SERIAL_2: D_U3003.29, D_U3004.4
/D_PROCESSOR/DAC_DATA_SRC: D_R1014.1, D_U1001.33
/D_PROCESSOR/LED_BLANK_SRC: D_R1013.1, D_U1001.15
/D_PROCESSOR/LED_MOSI_SRC: D_R1012.1, D_U1001.11
/D_PROCESSOR/LED_SCK_SRC: D_R1011.1, D_U1001.9
/D_PROCESSOR/LED_XLAT_SRC: D_R1010.1, D_U1001.8
/D_PROCESSOR/POT_ADC_00: D_C1011.1, D_R1031.2, D_R1041.1, D_U1001.22
/D_PROCESSOR/POT_ADC_01: D_C1012.1, D_R1032.2, D_R1042.1, D_U1001.23
/D_PROCESSOR/POT_ADC_02: D_C1013.1, D_R1033.2, D_R1043.1, D_U1001.24
/D_PROCESSOR/POT_ADC_03: D_C1014.1, D_R1034.2, D_R1044.1, D_U1001.25
/D_PROCESSOR/POT_ADC_04: D_C1015.1, D_R1035.2, D_R1045.1, D_U1001.26
/D_PROCESSOR/POT_ADC_05: D_C1016.1, D_R1036.2, D_R1046.1, D_U1001.27
/D_PROCESSOR/POT_ADC_06: D_C1017.1, D_R1037.2, D_R1047.1, D_U1001.28
/D_PROCESSOR/POT_ADC_07: D_C1018.1, D_R1038.2, D_R1048.1, D_U1001.29
/D_PROCESSOR/POT_ADC_08: D_C1019.1, D_R1039.2, D_R1049.1, D_U1001.30
/D_PROCESSOR/POT_ADC_09: D_C1020.1, D_R1040.2, D_R1050.1, D_U1001.31
/D_PROCESSOR/POT_RAW_00: D_J1020.2, D_R1031.1
/D_PROCESSOR/POT_RAW_01: D_J1021.2, D_R1032.1
/D_PROCESSOR/POT_RAW_02: D_J1022.2, D_R1033.1
/D_PROCESSOR/POT_RAW_03: D_J1023.2, D_R1034.1
/D_PROCESSOR/POT_RAW_04: D_J1024.2, D_R1035.1
/D_PROCESSOR/POT_RAW_05: D_J1025.2, D_R1036.1
/D_PROCESSOR/POT_RAW_06: D_J1026.2, D_R1037.1
/D_PROCESSOR/POT_RAW_07: D_J1027.2, D_R1038.1
/D_PROCESSOR/POT_RAW_08: D_J1028.2, D_R1039.1
/D_PROCESSOR/POT_RAW_09: D_J1029.2, D_R1040.1
/D_PROCESSOR/SDMMC_CLK: D_J1012.8, D_R1020.2
/D_PROCESSOR/SDMMC_CLK_SRC: D_R1020.1, D_U1001.7
/D_PROCESSOR/SDMMC_CMD: D_J1012.7, D_R1019.2
/D_PROCESSOR/SDMMC_CMD_SRC: D_R1019.1, D_U1001.6
/D_PROCESSOR/SDMMC_D0: D_J1012.3, D_R1015.2
/D_PROCESSOR/SDMMC_D0_SRC: D_R1015.1, D_U1001.5
/D_PROCESSOR/SDMMC_D1: D_J1012.4, D_R1016.2
/D_PROCESSOR/SDMMC_D1_SRC: D_R1016.1, D_U1001.4
/D_PROCESSOR/SDMMC_D2: D_J1012.5, D_R1017.2
/D_PROCESSOR/SDMMC_D2_SRC: D_R1017.1, D_U1001.3
/D_PROCESSOR/SDMMC_D3: D_J1012.6, D_R1018.2
/D_PROCESSOR/SDMMC_D3_SRC: D_R1018.1, D_U1001.2
/D_PROCESSOR/SEED_VIN: D_C1001.1, D_C1002.1, D_R1001.2, D_U1001.39
/D_PROCESSOR/V3V3_ANALOG: D_C1003.1, D_C1004.1, D_J1020.3, D_J1021.3, D_J1022.3, D_J1023.3, D_J1024.3, D_J1025.3, D_J1026.3, D_J1027.3, D_J1028.3, D_J1029.3, D_U1001.21
A__5V_DIG: A_C608.1, A_J702.1, A_K401.1, A_K503.1, A_K601.1, A_K602.1, A_U605.5
A__ADC_BIAS_WINDOW_OK: A_R142.2, A_U107.1, A_U107.2, A_U107.13, A_U107.14, A_U108.3, A_U211.2
A__ADC_DRV_ENABLE: A_R143.1, A_TP401.1, A_U210.4
A__ADC_LN: A_C103.2, A_C105.1, A_R103.1, A_R106.2, A_R111.1
A__ADC_LP: A_C103.1, A_C104.1, A_R104.1, A_R105.2, A_R110.1
A__ADC_RN: A_C117.2, A_C119.1, A_R119.1, A_R122.2, A_R127.1
A__ADC_RP: A_C117.1, A_C118.1, A_R120.1, A_R121.2, A_R126.1
A__CHIP_EN: A_R209.1, A_TP402.1, A_U207.12, A_U210.6
A__DAC_LN: A_C302.1, A_R302.1, A_U301.6
A__DAC_LP: A_C301.1, A_R301.1, A_U301.2
A__DAC_RN: A_C307.1, A_R314.1, A_U302.6
A__DAC_RP: A_C306.1, A_R313.1, A_U302.2
A__GAIN_LOW: A_D602.1, A_K401.8, A_K503.8, A_Q602.3
A__N12: A_C130.1, A_C132.1, A_C134.1, A_C312.1, A_C314.1, A_C316.1, A_C318.1, A_C320.1, A_C324.1, A_C406.1, A_C408.1, A_C508.1, A_C512.1, A_J701.5, A_U103.4, A_U104.11, A_U301.4, A_U302.4, A_U303.4, A_U304.4, A_U305.4, A_U401.4, A_U502.4
A__N19: A_C506.1, A_C510.1, A_J701.3, A_U501.4
A__P12: A_C129.1, A_C131.1, A_C133.1, A_C311.1, A_C313.1, A_C315.1, A_C317.1, A_C319.1, A_C323.1, A_C405.1, A_C407.1, A_C507.1, A_C511.1, A_J701.4, A_U103.8, A_U104.4, A_U301.8, A_U302.8, A_U303.8, A_U304.8, A_U305.8, A_U401.8, A_U502.8
A__P19: A_C505.1, A_C509.1, A_J701.1, A_U501.8
A__PRE_OUT_L: A_R107.1, A_R407.2, A_U103.3
A__PRE_OUT_R: A_R123.1, A_R414.2, A_U103.5
A__PROC_IN_L: A_K401.4, A_K602.3, A_R401.1
A__PROC_IN_R: A_K401.5, A_K602.6, A_R408.1
A__PROC_OUT_L: A_K503.3, A_K601.4
A__PROC_OUT_R: A_K503.6, A_K601.5
A__RECV_L: A_R312.2, A_R517.1, A_U501.3, A_U502.3
A__RECV_R: A_R324.2, A_R518.1, A_U501.5, A_U502.5
A__REF_ADC1: A_C212.1, A_C213.1, A_R108.1
A__REF_ADC2: A_C214.1, A_C215.1, A_R124.1
A__V5_REG: A_C112.1, A_C113.1, A_C126.1, A_C127.1, A_C135.1, A_C136.1, A_C216.1, A_C218.1, A_D101.2, A_D102.2, A_J701.6, A_R133.1, A_R134.1, A_R136.1, A_R138.1, A_R140.1, A_R142.1, A_U101.3, A_U102.3, A_U105.4, A_U106.4, A_U107.3, A_U108.5, A_U108.6, A_U202.1, A_U202.3, A_U203.1, A_U203.3
D__5V_DIG: D_C3001.1, D_C3002.1, D_C3003.1, D_C3004.1, D_C3005.1, D_C3006.1, D_C3007.1, D_C3008.1, D_C3010.1, D_C3012.1, D_C3013.1, D_C3014.1, D_J1001.1, D_J1013.1, D_J1014.1, D_J1015.1, D_J3002.25, D_J3002.26, D_J3003.25, D_J3003.26, D_J3004.25, D_J3004.26, D_J3005.25, D_J3005.26, D_R1001.1, D_R3007.2, D_R3011.2, D_U3001.32, D_U3002.32, D_U3003.32, D_U3004.32, D_U3005.23, D_U3005.24, D_U3007.3, D_U3007.5, D_U3007.6
D__LED_BLANK: D_R1002.1, D_R1013.2, D_R3010.1, D_U3005.6
D__LED_MOSI: D_R1012.2, D_R3019.1, D_U3005.3
D__LED_SCK: D_R1011.2, D_R3020.1, D_U3005.4
D__LED_XLAT: D_R1010.2, D_R3021.1, D_U3005.5
D__MODE_SEND_RETURN: D_J1004.2, D_J1008.2, D_U2003.21
LINK_ADC_DATA: A_J203.4, A_R216.2, D_J1005.4, D_U1001.32
LINK_AGND: A_C104.2, A_C105.2, A_C106.2, A_C109.2, A_C110.2, A_C111.2, A_C112.2, A_C113.2, A_C114.2, A_C118.2, A_C119.2, A_C120.2, A_C123.2, A_C124.2, A_C125.2, A_C126.2, A_C127.2, A_C128.2, A_C129.2, A_C130.2, A_C131.2, A_C132.2, A_C133.2, A_C134.2, A_C135.2, A_C136.2, A_C201.2, A_C202.2, A_C203.2, A_C204.2, A_C205.2, A_C206.2, A_C207.2, A_C208.2, A_C209.2, A_C210.2, A_C211.2, A_C212.2, A_C213.2, A_C214.2, A_C215.2, A_C216.2, A_C217.2, A_C218.2, A_C219.2, A_C220.2, A_C221.2, A_C222.2, A_C223.2, A_C224.2, A_C225.2, A_C226.2, A_C227.2, A_C228.2, A_C229.2, A_C230.2, A_C231.2, A_C232.2, A_C305.2, A_C310.2, A_C311.2, A_C312.2, A_C313.2, A_C314.2, A_C315.2, A_C316.2, A_C317.2, A_C318.2, A_C319.2, A_C320.2, A_C323.2, A_C324.2, A_C402.2, A_C404.2, A_C405.2, A_C406.2, A_C407.2, A_C408.2, A_C505.2, A_C506.2, A_C507.2, A_C508.2, A_C509.2, A_C510.2, A_C511.2, A_C512.2, A_C601.2, A_C602.2, A_C603.2, A_C604.2, A_C605.2, A_C606.2, A_C607.2, A_C608.2, A_C609.2, A_C610.2, A_C611.2, A_C612.2, A_D101.1, A_D102.1, A_D601.2, A_D602.2, A_D603.2, A_J203.1, A_J402.1, A_J402.7, A_J403.1, A_J602.1, A_J603.4, A_J606.1, A_J607.2, A_J608.2, A_J701.2, A_J702.2, A_Q601.2, A_Q602.2, A_Q603.2, A_R102.1, A_R107.2, A_R109.2, A_R118.1, A_R123.2, A_R125.2, A_R133.2, A_R139.2, A_R141.2, A_R144.2, A_R205.2, A_R206.2, A_R207.2, A_R208.2, A_R209.2, A_R210.2, A_R212.2, A_R311.2, A_R323.2, A_R325.2, A_R326.2, A_R402.2, A_R404.2, A_R406.2, A_R409.2, A_R411.2, A_R413.2, A_R502.2, A_R504.2, A_R506.2, A_R508.2, A_R510.2, A_R512.2, A_R514.2, A_R516.2, A_R517.2, A_R518.2, A_R602.2, A_R603.2, A_R604.2, A_R605.2, A_R607.2, A_R609.2, A_R611.2, A_R613.2, A_R614.2, A_R617.2, A_TP404.1, A_U105.2, A_U105.3, A_U105.5, A_U106.2, A_U106.3, A_U106.5, A_U107.12, A_U108.2, A_U202.2, A_U203.2, A_U204.2, A_U205.2, A_U206.2, A_U207.7, A_U208.2, A_U209.3, A_U210.2, A_U211.3, A_U212.3, A_U303.3, A_U303.5, A_U601.4, A_U601.9, A_U602.7, A_U603.4, A_U604.2, A_U605.2, A_U606.7, A_U607.2, A_U608.7, A_U608.9, A_U608.10, A_U608.12, A_U608.13, A_Y201.2, D_C1001.2, D_C1002.2, D_C1003.2, D_C1004.2, D_C1005.2, D_C1006.2, D_C1011.2, D_C1012.2, D_C1013.2, D_C1014.2, D_C1015.2, D_C1016.2, D_C1017.2, D_C1018.2, D_C1019.2, D_C1020.2, D_C2001.2, D_C2002.2, D_C2003.2, D_C2004.2, D_C3001.2, D_C3002.2, D_C3003.2, D_C3004.2, D_C3005.2, D_C3006.2, D_C3007.2, D_C3008.2, D_C3009.2, D_C3010.2, D_C3011.2, D_C3012.2, D_C3013.2, D_C3014.2, D_J1001.2, D_J1003.1, D_J1004.1, D_J1005.1, D_J1006.1, D_J1007.1, D_J1008.1, D_J1009.1, D_J1010.1, D_J1012.1, D_J1013.2, D_J1014.2, D_J1015.2, D_J1020.1, D_J1021.1, D_J1022.1, D_J1023.1, D_J1024.1, D_J1025.1, D_J1026.1, D_J1027.1, D_J1028.1, D_J1029.1, D_J2001.15, D_J2001.16, D_J2002.15, D_J2002.16, D_J2003.1, D_Q3002.2, D_R1003.2, D_R1004.2, D_R1005.2, D_R1006.2, D_R1041.2, D_R1042.2, D_R1043.2, D_R1044.2, D_R1045.2, D_R1046.2, D_R1047.2, D_R1048.2, D_R1049.2, D_R1050.2, D_R2001.2, D_R2002.2, D_R2003.2, D_R3001.2, D_R3002.2, D_R3003.2, D_R3004.2, D_R3008.2, D_R3009.2, D_R3012.2, D_R3013.2, D_R3014.2, D_R3019.2, D_R3020.2, D_R3021.2, D_U1001.20, D_U1001.40, D_U2001.10, D_U2001.15, D_U2001.16, D_U2001.17, D_U2002.10, D_U2002.16, D_U2002.17, D_U2003.10, D_U2003.15, D_U2003.17, D_U3001.1, D_U3001.33, D_U3002.1, D_U3002.33, D_U3003.1, D_U3003.33, D_U3004.1, D_U3004.33, D_U3005.7, D_U3005.8, D_U3005.9, D_U3005.10, D_U3005.11, D_U3005.12, D_U3005.13, D_U3006.2, D_U3007.2
LINK_ANALOG_OK: A_J402.6, A_J402.10, A_J603.3, A_R210.1, A_R605.1, A_U209.4, A_U602.2, D_J1004.4, D_J1006.6, D_R2002.1, D_U2003.23
LINK_ARMED: A_J602.5, A_U602.9, A_U603.3, D_J1003.5, D_R1005.1, D_U1001.37
LINK_BCLK: A_J203.2, A_R214.2, D_J1005.2, D_U1001.35
LINK_BYPASS_SENSE: A_J602.6, A_J603.5, A_R606.2, D_J1003.6, D_J1004.3, D_U2003.22
LINK_CODEC_RUN: A_J402.5, A_R205.1, A_U207.5, D_J1006.5, D_R1006.1, D_R2001.1, D_U1001.1, D_U2001.18, D_U2002.18, D_U2003.18
LINK_DAC_DATA: A_J203.5, D_J1005.5, D_R1014.2
LINK_GAIN_REQ: A_J602.4, A_R607.1, A_R610.1, A_R615.1, A_U608.1, D_J1003.4, D_R1004.1, D_U1001.10
LINK_HEARTBEAT: A_J602.2, A_R602.1, A_U601.6, D_J1003.2, D_U1001.14
LINK_INPUT_READY: A_J606.2, A_U606.3, A_U606.9, D_J1004.5, D_J1007.2, D_R2003.1, D_U2003.24
LINK_MCU_PERMIT: A_J602.3, A_R603.1, A_U602.12, A_U602.13, D_J1003.3, D_R1003.1, D_U1001.36
LINK_SCL: A_J402.3, A_R201.1, D_J1006.3, D_J1009.3, D_J1010.3, D_U1001.12, D_U2001.12, D_U2002.12, D_U2003.12
LINK_SDA: A_J402.4, A_R202.1, D_J1006.4, D_J1009.4, D_J1010.4, D_U1001.13, D_U2001.13, D_U2002.13, D_U2003.13
LINK_V3V3_IO: A_C201.1, A_C220.1, A_C221.1, A_C222.1, A_C223.1, A_C224.1, A_C225.1, A_C226.1, A_C228.1, A_C230.1, A_C231.1, A_C232.1, A_C602.1, A_C603.1, A_C604.1, A_C605.1, A_C606.1, A_C607.1, A_C610.1, A_C611.1, A_C612.1, A_J402.2, A_J603.1, A_R201.2, A_R202.2, A_R203.2, A_R204.2, A_R601.1, A_R606.1, A_R616.1, A_R618.1, A_U204.1, A_U204.3, A_U204.4, A_U205.3, A_U205.4, A_U206.3, A_U206.4, A_U207.14, A_U208.1, A_U208.4, A_U209.5, A_U210.5, A_U211.5, A_U212.5, A_U601.1, A_U601.3, A_U601.5, A_U602.14, A_U603.2, A_U603.7, A_U603.8, A_U604.3, A_U604.5, A_U604.6, A_U605.3, A_U605.6, A_U606.14, A_U607.5, A_U608.5, A_U608.14, A_Y201.1, A_Y201.4, D_C1005.1, D_C1006.1, D_C2001.1, D_C2002.1, D_C2003.1, D_C2004.1, D_C3009.1, D_C3011.1, D_J1006.2, D_J1009.2, D_J1010.2, D_J1012.2, D_R1002.2, D_R3005.2, D_R3006.2, D_R3010.2, D_U1001.38, D_U2001.9, D_U2002.9, D_U2002.15, D_U2003.9, D_U2003.16, D_U3005.1, D_U3005.2, D_U3006.3, D_U3006.5, D_U3006.6
LINK_WS: A_J203.3, A_R215.2, D_J1005.3, D_U1001.34
